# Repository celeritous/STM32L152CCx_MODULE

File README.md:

Thid repository contains the hardware design and firmware templates for Celeritous' newest processor module. This board is based on the ST Micro Cortex M3 Low power STM32L151/152 processor line. 

It is being released as Open Source Hardware under the CERN OSH License ver 1.2

All hardware design files are in KiCAD format

All Firmware files will be based on code generated by and for the STM32MXCube code initialization generator and Atollic TrueStudio development environment. 

If users wish to adapt this for use with the Arduino environment they are welcome to do so and we will gladly post it, but our main focus will continue to be based on the TrueStudio environment.

The board has the following features:
1. Small form factor 2.0" x 0.800" (same form factor as STM32F103 "Blue Pill" board but is NOT pin compatible
2. 2 x 20 pin 0.100" pitch headers spaced 0.700 apart (Different spacing than Blue Pill)
3. On-board 3.3V regulator to allow +5V external power
4. External +3.3V power also accepted
5. Board power source is jumper selectable between un-regulated external +5 or external regulated +3.3V
6. Regulated, fused +3.3V power available for user when +5V input is used
7. Power inputs are fused, inverse voltage protected and overvoltage protected
8. 1 USB host/client port with Mini-B connector soldered to board - won't shear off board
9. USB port transient protected, includes 1.5K pull-up 
10. USB port is by default un-powered but may be powered from +5V or +3.3V by installing jumper
11. Board cannot be powered from the USB port. Power is diode isolated to block external USB port sopurces.
12. 65K On-board I2C EEPROM (8K x 8) included. May be upgraded to 256K (32K x 8)
13. 12MHz and 32kHz crystals both included to allow use of RTC
14. VBATT input provided to keep RTC alive during loss of power
15. Power and User defined LEDs
16. On-board I2C Pull-ups included for I2C1 bus which is used for the EEPROM
17. On-Board momentary reset switch
18. On-board Boot mode jumper
19. On-board SWDIO header for ST-Lin V2 Programmer/Debugger module
20. STM32L152CC Processor with 256Kbytes of flash memory and up to 32MHz internal clock speed in LQFP-48 package
21. 4 Layer board for low EMI/RFI

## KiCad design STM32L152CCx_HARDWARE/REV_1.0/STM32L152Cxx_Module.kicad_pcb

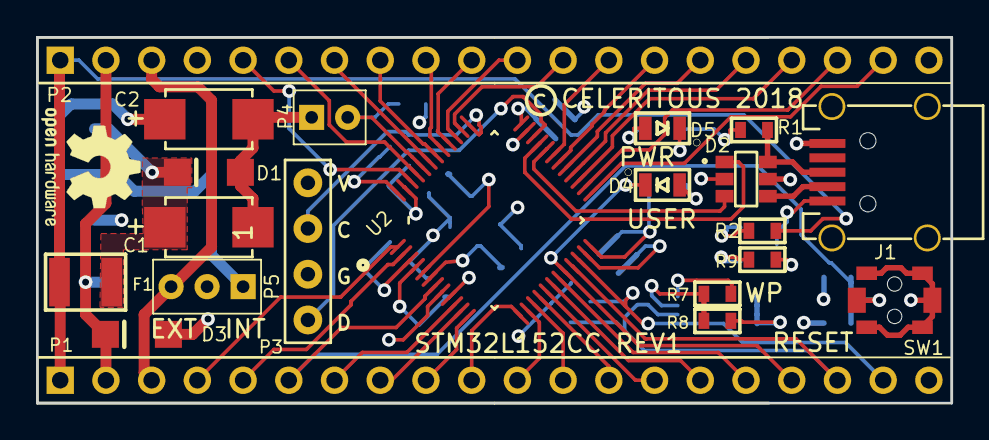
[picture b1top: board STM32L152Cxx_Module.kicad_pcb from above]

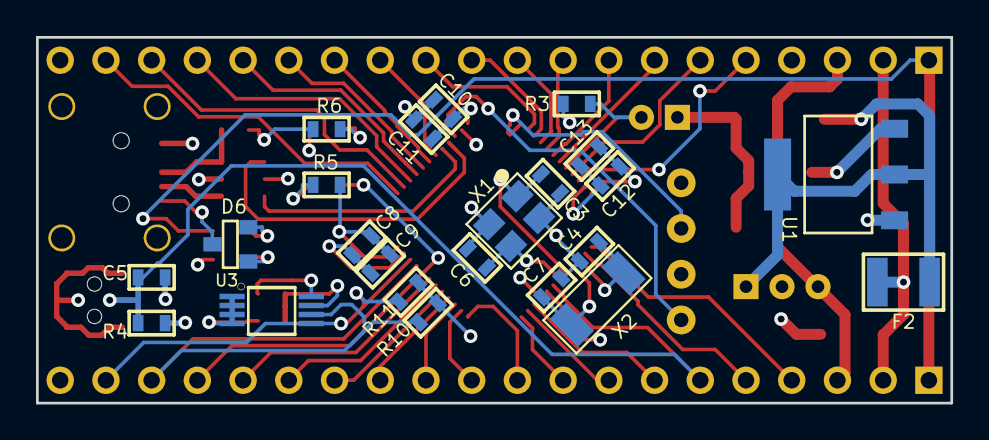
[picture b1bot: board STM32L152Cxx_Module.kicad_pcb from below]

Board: 4 copper layers, 50.8 x 20.3 mm, 45 parts (23 on the bottom side), 55 nets.

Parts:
C1, C2: 47uF; CAPACITOR_TANTALUM_C
C3, C4, C6, C7: 12pF; P0603
C5: 0.010uF; P0603
C8, C10, C12: 0.10uF; P0603
C9, C11, C13: 10.0uF; P0603
D1, D3: SMLJ33ABCT; MINI_SMA
D2: USBLC6-2; SOT23-6
D4, D5: Led_Small; D0805
D6: BAT54C; SOT23-3
F1: FUSE_PTC_.75A_33V; P1210
F2: FUSE_PTC_.5A_33V; P1210
J1: USB_MINI_B_SMD; CONN_USB_UX60-MB
P1, P2: CONN_1x20; HEADER_1X20_100MIL
P3: CONN_1x4; Connector_1x4_100mil_TH
P4: Header_2x1; HEADER_1X2_2MM
P5: CONN_1x3; HEADER_1X3_2MM
R1: 1.50kΩ; P0603
R2, R7, R9: ZERO_Ω; P0603
R3, R4: 10.0kΩ; P0603
R5, R6: 220.0Ω; P0603
R8: 4.70kΩ; P0603
R10, R11: 3.30kΩ; P0603
REF00: OSHW-Logo2_7.3x6mm_SilkScreen
SW1: PUSHBUTTON_SPST_3X4MM; SWITCH_SPST_3X4MM
U1: LM1117_SOT223; SOT223_4
U2: STM32L152Cxx; QFP48_7X7_0.5
U3: 24FCxx_/MS; MSOP8
X1: ABM8G-12.00MHz; XTAL_3.2X2.5
X2: ABS10-32.768kHz; XTAL_1.8X4.9mm

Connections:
+3.3V: C8.1, C9.1, C10.1, C11.1, C12.1, C13.1, D2.5, P3.4, P5.2, R1.1, R3.2, R4.2, R5.1, R6.1, R7.1, R9.1, R10.2, R11.2, U2.9, U2.24, U2.36, U2.48, U3.8
+5V: F1.1, P1.1, P2.1, R2.1
/+3.3V_IN: P1.3, P2.3, P5.3
/+3.3V_INT: C2.1, F2.1, P5.1, U1.2, U1.4
/+3.3V_OUT: D3.K, F2.2, P1.2, P2.2
/BOOT: P4.2, R3.1, U2.44
/PA0: P1.7, U2.10
/PA1: P1.8, U2.11
/PA2: P1.9, U2.12
/PA3: P1.10, U2.13
/PA4: P1.11, U2.14
/PA5: P1.12, U2.15
/PA6: P1.13, U2.16
/PA7: P1.14, U2.17
/PA8: P2.15, U2.29
/PA9: P2.14, U2.30
/PA10: P2.13, U2.31
/PA15: P2.12, U2.38
/PB0: P1.15, U2.18
/PB1: P1.16, U2.19
/PB2: D4.K, P1.17, U2.20
/PB3: P2.11, U2.39
/PB4: P2.10, U2.40
/PB5: P2.9, U2.41
/PB6: P2.8, U2.42
/PB7: P2.7, U2.43
/PB8: P2.6, U2.45
/PB9: P2.5, U2.46
/PB10: P1.18, R10.1, U2.21, U3.6
/PB11: P1.19, R11.1, U2.22, U3.5
/PB12: P2.19, U2.25
/PB13: P2.18, U2.26
/PB14: P2.17, U2.27
/PB15: P2.16, U2.28
/PC13: P1.5, U2.2
/SWCLK: P3.3, U2.37
/SWDIO: P3.1, U2.34
/USB_DM: D2.3, U2.32
/USB_DP: D2.1, U2.33
/VBAT: P1.4, U2.1
/WP: R7.2, R8.1, U3.7
/X1: C3.1, U2.5, X1.1
/X2: C6.1, U2.6, X1.3
/X3: C4.1, U2.3, X2.1
/X4: C7.1, U2.4, X2.2
/~MRST: C5.1, P1.6, R4.1, SW1.2, U2.7
GND: C1.2, C2.2, C3.2, C4.2, C5.2, C6.2, C7.2, C8.2, C9.2, C10.2, C11.2, C12.2, C13.2, D1.A, D2.2, D3.A, D5.K, J1.5, J1.6, J1.7, J1.8, J1.9, P1.20, P2.20, P3.2, P4.1, R8.2, SW1.1, SW1.3, SW1.4, SW1.5, SW1.6, U1.1, U2.8, U2.23, U2.35, U2.47, U3.1, U3.2, U3.3, U3.4, X1.2, X1.4
unnamed: C1.1, D1.K, F1.2, U1.3
unnamed: D2.4, J1.2
unnamed: D2.6, J1.3, R1.2
unnamed: D4.A, R5.2
unnamed: D5.A, R6.2
unnamed: D6.1, R9.2
unnamed: D6.2, J1.1
unnamed: D6.3, R2.2

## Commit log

2018-05-24 Initial Commit
    For review and comment
2018-06-25 Revision 1.1 with open issues corrected & closed
2018-07-05 Update 7/4/2018

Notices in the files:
STM32L152CCx_HARDWARE/REV_1.0/STM32L152Cxx_Module.kicad_pcb:
COPYRIGHT 2018 ALL RIGHTS RESERVED
